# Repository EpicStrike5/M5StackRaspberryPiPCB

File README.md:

# M5StackRaspberryPiPCB
A simple dev board for using decentralized I/O port from the both of them 

I created this PCB for the sole purpose of decentralizing the I/O port for both the M5Stack Gray and the Raspberry Pi4. The intent is that it's easier to develop on a breadboard with a "fixed" Pi or M5. 

The gist is that we have female header and we decide to populate half of the pin holes ith header. In the case of a 1x2 Header, we solder a 1P header and leaves one hole free so that we can plug rigid cable if we don't want to use jumpers.

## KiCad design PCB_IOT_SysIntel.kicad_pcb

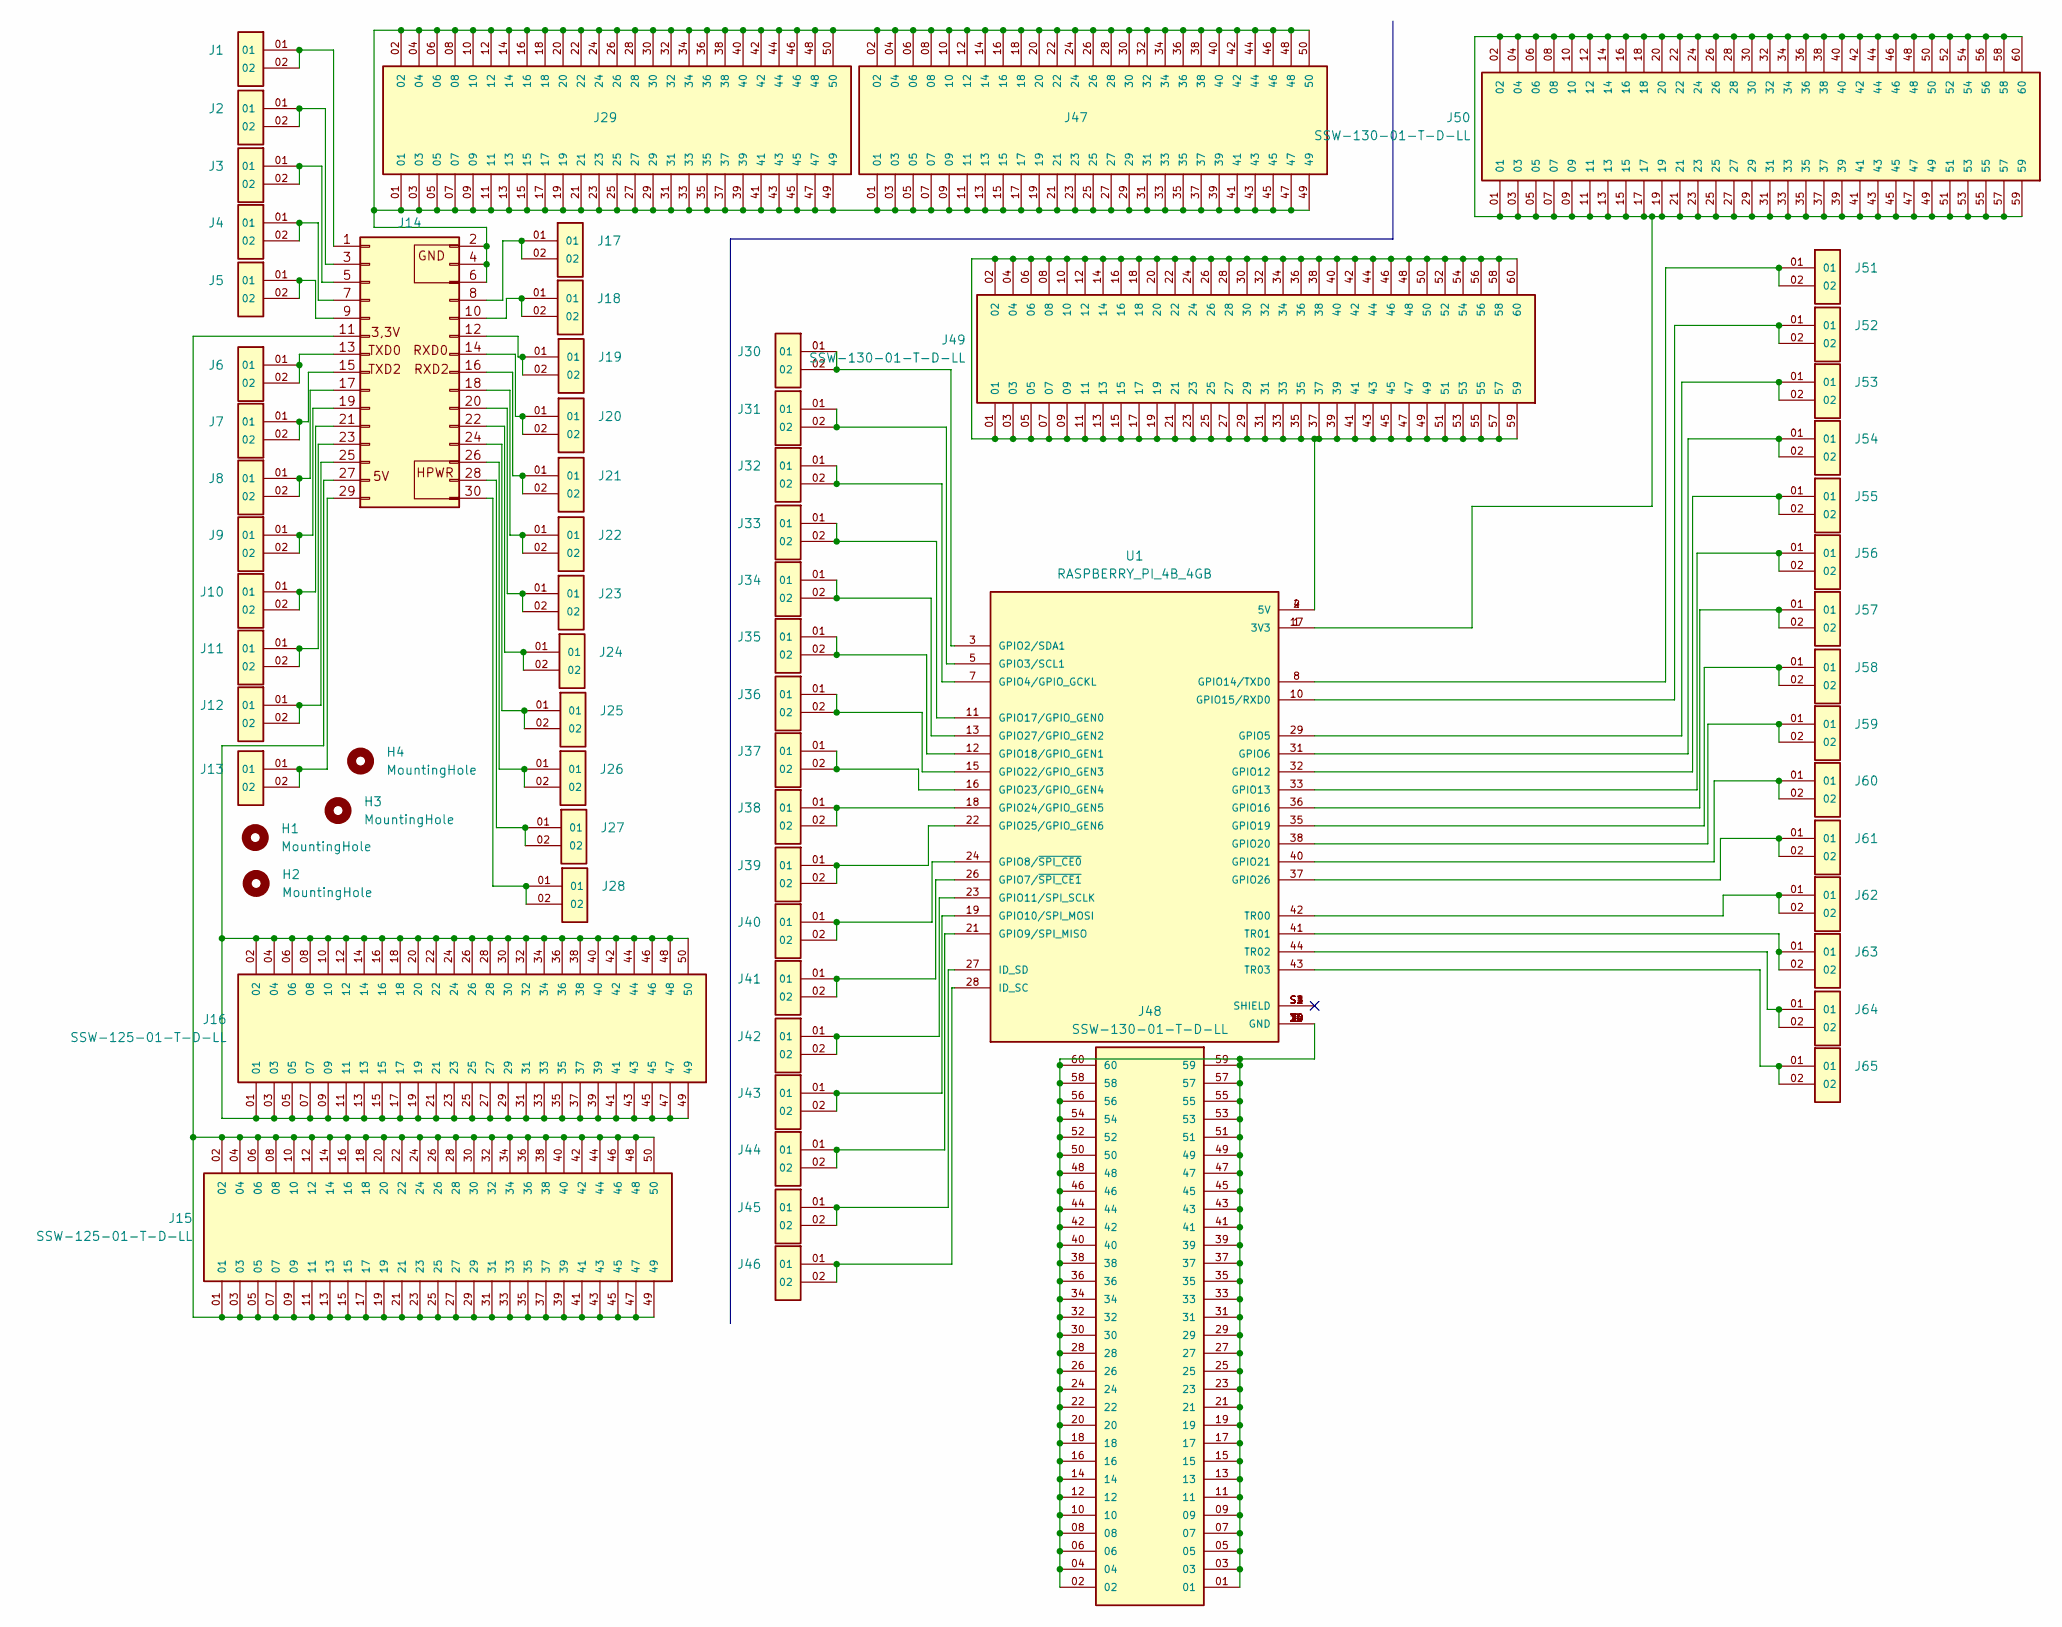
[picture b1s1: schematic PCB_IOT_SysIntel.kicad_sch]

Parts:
H1, H2, H3, H4: MountingHole; MountingHole_3.2mm_M3
J1, J2, J3, J4, J5, J6, J7, J8, J9, J10, J11, J12, J13, J17, J18, J19, J20, J21, J22, J23, J24, J25, J26, J27, J28, J30, J31, J32, J33, J34, J35, J36, J37, J38, J39, J40, J41, J42, J43, J44, J45, J46, J51, J52, J53, J54, J55, J56, J57, J58, J59, J60, J61, J62, J63, J64, J65: SSW-102-02-G-S; SAMTEC_SSW-102-02-G-S-Populated; PARTREV R
J14: M5Stack
J15, J16, J29: SSW-125-01-T-D-LL; SAMTEC_SSW-125-01-T-D-LL-Populated; PARTREV R
J47: SSW-125-01-T-D-LL; SAMTEC_SSW-125-01-T-D-LL; PARTREV R
J48, J49, J50: SSW-130-01-T-D-LL; SAMTEC_SSW-130-01-T-D-LL; PARTREV R
U1: RASPBERRY_PI_4B_4GB; MODULE_RASPBERRY_PI_4B_4GB; PARTREV 4

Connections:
unnamed: J1.01, J1.02, J14.1
unnamed: J14.2, J14.4, J14.6, J29.01, J29.02, J29.03, J29.04, J29.05, J29.06, J29.07, J29.08, J29.09, J29.10, J29.11, J29.12, J29.13, J29.14, J29.15, J29.16, J29.17, J29.18, J29.19, J29.20, J29.21, J29.22, J29.23, J29.24, J29.25, J29.26, J29.27, J29.28, J29.29, J29.30, J29.31, J29.32, J29.33, J29.34, J29.35, J29.36, J29.37, J29.38, J29.39, J29.40, J29.41, J29.42, J29.43, J29.44, J29.45, J29.46, J29.47, J29.48, J29.49, J29.50, J47.01, J47.02, J47.03, J47.04, J47.05, J47.06, J47.07, J47.08, J47.09, J47.10, J47.11, J47.12, J47.13, J47.14, J47.15, J47.16, J47.17, J47.18, J47.19, J47.20, J47.21, J47.22, J47.23, J47.24, J47.25, J47.26, J47.27, J47.28, J47.29, J47.30, J47.31, J47.32, J47.33, J47.34, J47.35, J47.36, J47.37, J47.38, J47.39, J47.40, J47.41, J47.42, J47.43, J47.44, J47.45, J47.46, J47.47, J47.48, J47.49, J47.50
unnamed: J2.01, J2.02, J14.3
unnamed: J3.01, J3.02, J14.5
unnamed: J4.01, J4.02, J14.7
unnamed: J14.8, J17.01, J17.02
unnamed: J5.01, J5.02, J14.9
unnamed: J14.10, J18.01, J18.02
unnamed: J14.11, J15.01, J15.02, J15.03, J15.04, J15.05, J15.06, J15.07, J15.08, J15.09, J15.10, J15.11, J15.12, J15.13, J15.14, J15.15, J15.16, J15.17, J15.18, J15.19, J15.20, J15.21, J15.22, J15.23, J15.24, J15.25, J15.26, J15.27, J15.28, J15.29, J15.30, J15.31, J15.32, J15.33, J15.34, J15.35, J15.36, J15.37, J15.38, J15.39, J15.40, J15.41, J15.42, J15.43, J15.44, J15.45, J15.46, J15.47, J15.48, J15.49, J15.50
unnamed: J14.12, J19.01, J19.02
unnamed: J6.01, J6.02, J14.13
unnamed: J14.14, J20.01, J20.02
unnamed: J7.01, J7.02, J14.15
unnamed: J14.16, J21.01, J21.02
unnamed: J8.01, J8.02, J14.17
unnamed: J14.18, J22.01, J22.02
unnamed: J9.01, J9.02, J14.19
unnamed: J14.20, J23.01, J23.02
unnamed: J10.01, J10.02, J14.21
unnamed: J14.22, J24.01, J24.02
unnamed: J11.01, J11.02, J14.23
unnamed: J14.24, J25.01, J25.02
unnamed: J12.01, J12.02, J14.25
unnamed: J14.26, J26.01, J26.02
unnamed: J14.27, J16.01, J16.02, J16.03, J16.04, J16.05, J16.06, J16.07, J16.08, J16.09, J16.10, J16.11, J16.12, J16.13, J16.14, J16.15, J16.16, J16.17, J16.18, J16.19, J16.20, J16.21, J16.22, J16.23, J16.24, J16.25, J16.26, J16.27, J16.28, J16.29, J16.30, J16.31, J16.32, J16.33, J16.34, J16.35, J16.36, J16.37, J16.38, J16.39, J16.40, J16.41, J16.42, J16.43, J16.44, J16.45, J16.46, J16.47, J16.48, J16.49, J16.50
unnamed: J14.28, J27.01, J27.02
unnamed: J13.01, J13.02, J14.29
unnamed: J14.30, J28.01, J28.02
unnamed: J48.01, J48.02, J48.03, J48.04, J48.05, J48.06, J48.07, J48.08, J48.09, J48.10, J48.11, J48.12, J48.13, J48.14, J48.15, J48.16, J48.17, J48.18, J48.19, J48.20, J48.21, J48.22, J48.23, J48.24, J48.25, J48.26, J48.27, J48.28, J48.29, J48.30, J48.31, J48.32, J48.33, J48.34, J48.35, J48.36, J48.37, J48.38, J48.39, J48.40, J48.41, J48.42, J48.43, J48.44, J48.45, J48.46, J48.47, J48.48, J48.49, J48.50, J48.51, J48.52, J48.53, J48.54, J48.55, J48.56, J48.57, J48.58, J48.59, J48.60, U1.6 (GND), U1.9 (GND), U1.14 (GND), U1.20 (GND), U1.25 (GND), U1.30 (GND), U1.34 (GND), U1.39 (GND)
unnamed: J49.01, J49.02, J49.03, J49.04, J49.05, J49.06, J49.07, J49.08, J49.09, J49.10, J49.11, J49.12, J49.13, J49.14, J49.15, J49.16, J49.17, J49.18, J49.19, J49.20, J49.21, J49.22, J49.23, J49.24, J49.25, J49.26, J49.27, J49.28, J49.29, J49.30, J49.31, J49.32, J49.33, J49.34, J49.35, J49.36, J49.37, J49.38, J49.39, J49.40, J49.41, J49.42, J49.43, J49.44, J49.45, J49.46, J49.47, J49.48, J49.49, J49.50, J49.51, J49.52, J49.53, J49.54, J49.55, J49.56, J49.57, J49.58, J49.59, J49.60, U1.2 (5V), U1.4 (5V)
unnamed: J50.01, J50.02, J50.03, J50.04, J50.05, J50.06, J50.07, J50.08, J50.09, J50.10, J50.11, J50.12, J50.13, J50.14, J50.15, J50.16, J50.17, J50.18, J50.19, J50.20, J50.21, J50.22, J50.23, J50.24, J50.25, J50.26, J50.27, J50.28, J50.29, J50.30, J50.31, J50.32, J50.33, J50.34, J50.35, J50.36, J50.37, J50.38, J50.39, J50.40, J50.41, J50.42, J50.43, J50.44, J50.45, J50.46, J50.47, J50.48, J50.49, J50.50, J50.51, J50.52, J50.53, J50.54, J50.55, J50.56, J50.57, J50.58, J50.59, J50.60, U1.1 (3V3), U1.17 (3V3)
unnamed: J30.01, J30.02, U1.3 (GPIO2/SDA1)
unnamed: J31.01, J31.02, U1.5 (GPIO3/SCL1)
unnamed: J32.01, J32.02, U1.7 (GPIO4/GPIO_GCKL)
unnamed: J53.01, J53.02, U1.29 (GPIO5)
unnamed: J54.01, J54.02, U1.31 (GPIO6)
unnamed: J41.01, J41.02, U1.26 (GPIO7/~SPI_CE1)
unnamed: J40.01, J40.02, U1.24 (GPIO8/~SPI_CE0)
unnamed: J44.01, J44.02, U1.21 (GPIO9/SPI_MISO)
unnamed: J43.01, J43.02, U1.19 (GPIO10/SPI_MOSI)
unnamed: J42.01, J42.02, U1.23 (GPIO11/SPI_SCLK)
unnamed: J55.01, J55.02, U1.32 (GPIO12)
unnamed: J56.01, J56.02, U1.33 (GPIO13)
unnamed: J51.01, J51.02, U1.8 (GPIO14/TXD0)
unnamed: J52.01, J52.02, U1.10 (GPIO15/RXD0)
unnamed: J57.01, J57.02, U1.36 (GPIO16)
unnamed: J33.01, J33.02, U1.11 (GPIO17/GPIO_GEN0)
unnamed: J35.01, J35.02, U1.12 (GPIO18/GPIO_GEN1)
unnamed: J58.01, J58.02, U1.35 (GPIO19)
unnamed: J59.01, J59.02, U1.38 (GPIO20)
unnamed: J60.01, J60.02, U1.40 (GPIO21)
unnamed: J36.01, J36.02, U1.15 (GPIO22/GPIO_GEN3)
unnamed: J37.01, J37.02, U1.16 (GPIO23/GPIO_GEN4)
unnamed: J38.01, J38.02, U1.18 (GPIO24/GPIO_GEN5)
unnamed: J39.01, J39.02, U1.22 (GPIO25/GPIO_GEN6)
unnamed: J61.01, J61.02, U1.37 (GPIO26)
unnamed: J34.01, J34.02, U1.13 (GPIO27/GPIO_GEN2)
unnamed: J46.01, J46.02, U1.28 (ID_SC)
unnamed: J45.01, J45.02, U1.27 (ID_SD)
unnamed: J62.01, J62.02, U1.42 (TR00)
unnamed: J63.01, J63.02, U1.41 (TR01)
unnamed: J64.01, J64.02, U1.44 (TR02)
unnamed: J65.01, J65.02, U1.43 (TR03)

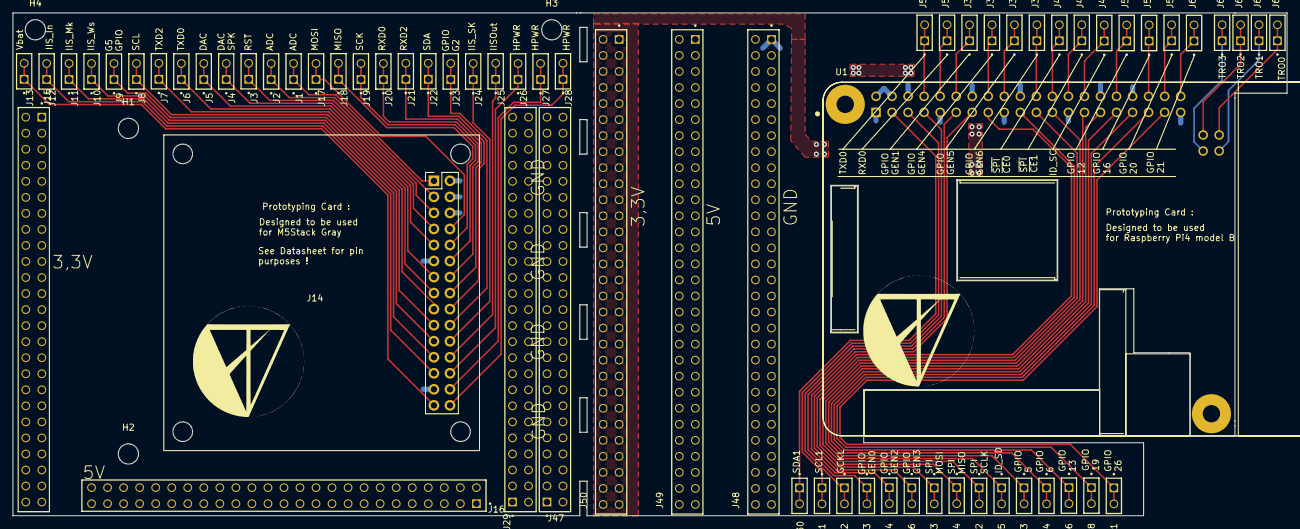
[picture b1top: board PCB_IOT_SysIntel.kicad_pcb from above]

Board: 2 copper layers, 201.8 x 79.6 mm, 70 parts (0 on the bottom side), 63 nets.

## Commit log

2024-05-18 First Commit :
    Created libraries with header
2024-05-21 Project Version 1 Completed
2024-05-22 Fixed Mounting hole issues
